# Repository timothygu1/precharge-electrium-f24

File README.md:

# 10S Precharge/Antispark PCB

For limiting inrush current during connection of a 10S (42V nominal) lithium-ion battery pack to motor controllers.
Featuring RC-timed MOSFET gate driver, SPDT switch control, removable fuse & copper busbar support.

### Top 3D View

### Top Layer

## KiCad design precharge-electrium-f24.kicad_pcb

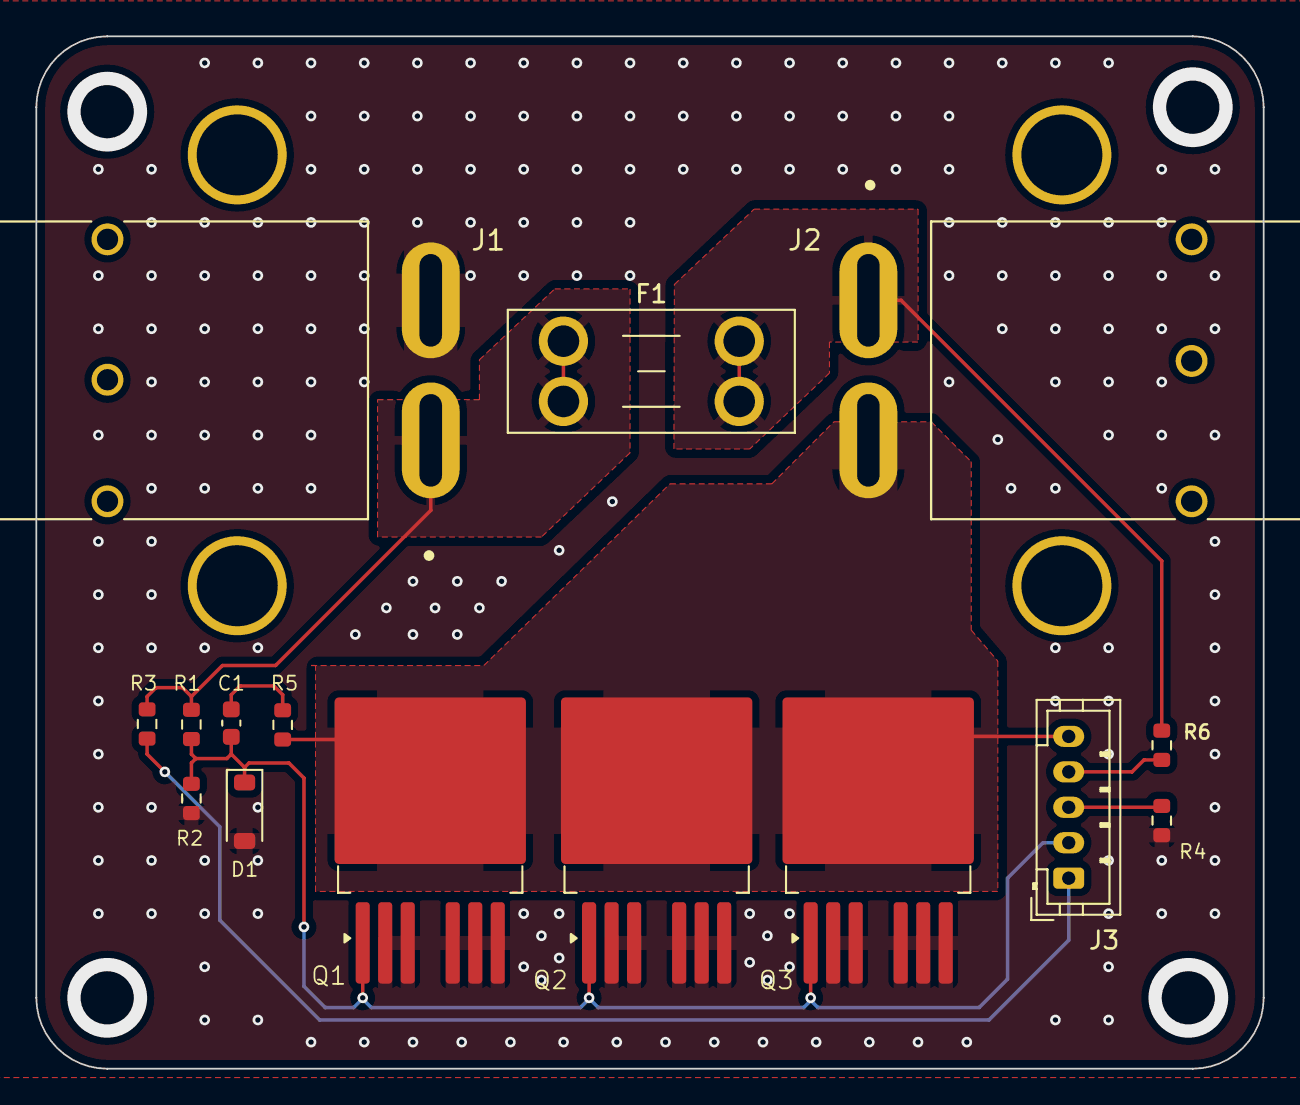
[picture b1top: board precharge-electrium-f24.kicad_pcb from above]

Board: 2 copper layers, 69.2 x 58.2 mm, 15 parts (0 on the bottom side), 9 nets.

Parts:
C1: 1uF, 0603, 60V, X7R; C_0603_1608Metric
D1: 12V, 200mW, SOD-123; D_SOD-123
F1: 3568; Fuseholder_Blade_Mini_Keystone_3568
J1, J2: ASMPR45-1X2-RK; APP_ASMPR45-1X2-RK
J3: B5B-PH-K-S; JST_PH_B5B-PH-K_1x05_P2.00mm_Vertical
Q1, Q2, Q3: IRFS7530; Package_TO_SOT_SMDTO-263-6-CUSTOM
R1, R2: 1M; R_0603_1608Metric
R3, R6: 10k; R_0603_1608Metric
R4: 100; R_0603_1608Metric
R5: 1k; R_0603_1608Metric

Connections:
/+LED: J3.4, R6.2
/NC: J3.3, R4.1
/NO: J3.1, R3.2
/SW: C1.2, D1.1 (K), J3.2, Q1.1 (G), Q2.1 (G), Q3.1 (G), R1.2, R2.1
GND: D1.2 (A), J1.2, Q1.2 (S), Q1.3 (S), Q1.5 (S), Q1.6 (S), Q1.7 (S), Q2.2 (S), Q2.3 (S), Q2.5 (S), Q2.6 (S), Q2.7 (S), Q3.2 (S), Q3.3 (S), Q3.5 (S), Q3.6 (S), Q3.7 (S), R2.2, R4.2
unnamed: C1.1, R5.1
OUT+: F1.2, J2.1, R6.1
OUT-: J2.2, J3.5, Q1.4 (D), Q2.4 (D), Q3.4 (D), R5.2
VCC: F1.1, J1.1, R1.1, R3.1

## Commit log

2025-05-09 Update PCB layout and fix rules violations
2025-05-09 Add gerbers
